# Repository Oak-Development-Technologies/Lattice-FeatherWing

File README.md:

# Lattice FeatherWing
<image src=/images/lattice%20featherwing%20front.jpg>
Home of the Lattice FeatherWing

Lattice FeatherWing is an iCE5LP4K FeatherWing designed to be a companion to any Adafruit compatible feather development board available. Lattice FeatherWing provides 35 IO to 0.1" headers which can be used with dupont 0.1" cables to hook into a companion breadboard.

Interested? You can purchase the Lattice FeatherWing on [Tindie](https://www.tindie.com/products/34549/)

# Quick Facts about Lattice FeatherWing:

* 35 IO Exposed to 0.1" headers 
* 9 IO (including SPI programming pins) directly available to interface with host Feather.
* Small yet bright UHD1110 RGB LED
* 2.5V provided for NVCM programming
* Edge reachable reset button that solely resets the FPGA

# Pinout Card

Provided below is the pinout card that should ship with all Lattice FeatherWing. If you didn't get one, you can always print off the pinout card from the pinout card image in the [images](/images) directory of this repository.

<image src=/images/Lattice%20FeatherWing%20Pincard.jpg>

As noted on the pinout card, each pin on the Lattice FeatherWing corresponds to the phyiscal pin on the FPGA IC. These phyiscal pins are used in the [io.pcf](/examples/common/io.pcf) file to help make it easier for you to pick pins for input/outputs of your verilog designs. These pin numbers can be used to create pin groupings like in the io.pcf file to make it easier to generate your own designs.

# Some Quick Links

You can find some Lattice FeatherWing specific examples by clicking [here](/examples). These examples can be built with the included io.pcf and Makefile by using various make commands. (currently just RGB PWM example available).

In addition to the examples in this repository, you can also find examples for the iCE5LP4K in this [ice5lp4k_examples repository](https://github.com/skerr92/ice5lp4k_examples).

If you're interested in CPU design, you can checkout the [O2 Trainer CPU](https://github.com/skerr92/O2-Trainer).

The KiCAD board files and manufacturing files can be found by clicking [here](/Board%20Files/). These include all the information you need to make your own Lattice FPGA board, or order the files yourself if you want the challenge of making your own.

Lattice FeatherWing is Licensed under [MIT License](LICENSE). This license is permissive, and the contents of this repository come AS IS. Please see the License file for additonal details.

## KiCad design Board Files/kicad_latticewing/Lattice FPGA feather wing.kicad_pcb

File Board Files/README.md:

Find relevant schematic and board files here.

These are the latest revision available, you can open them directly in kicad.

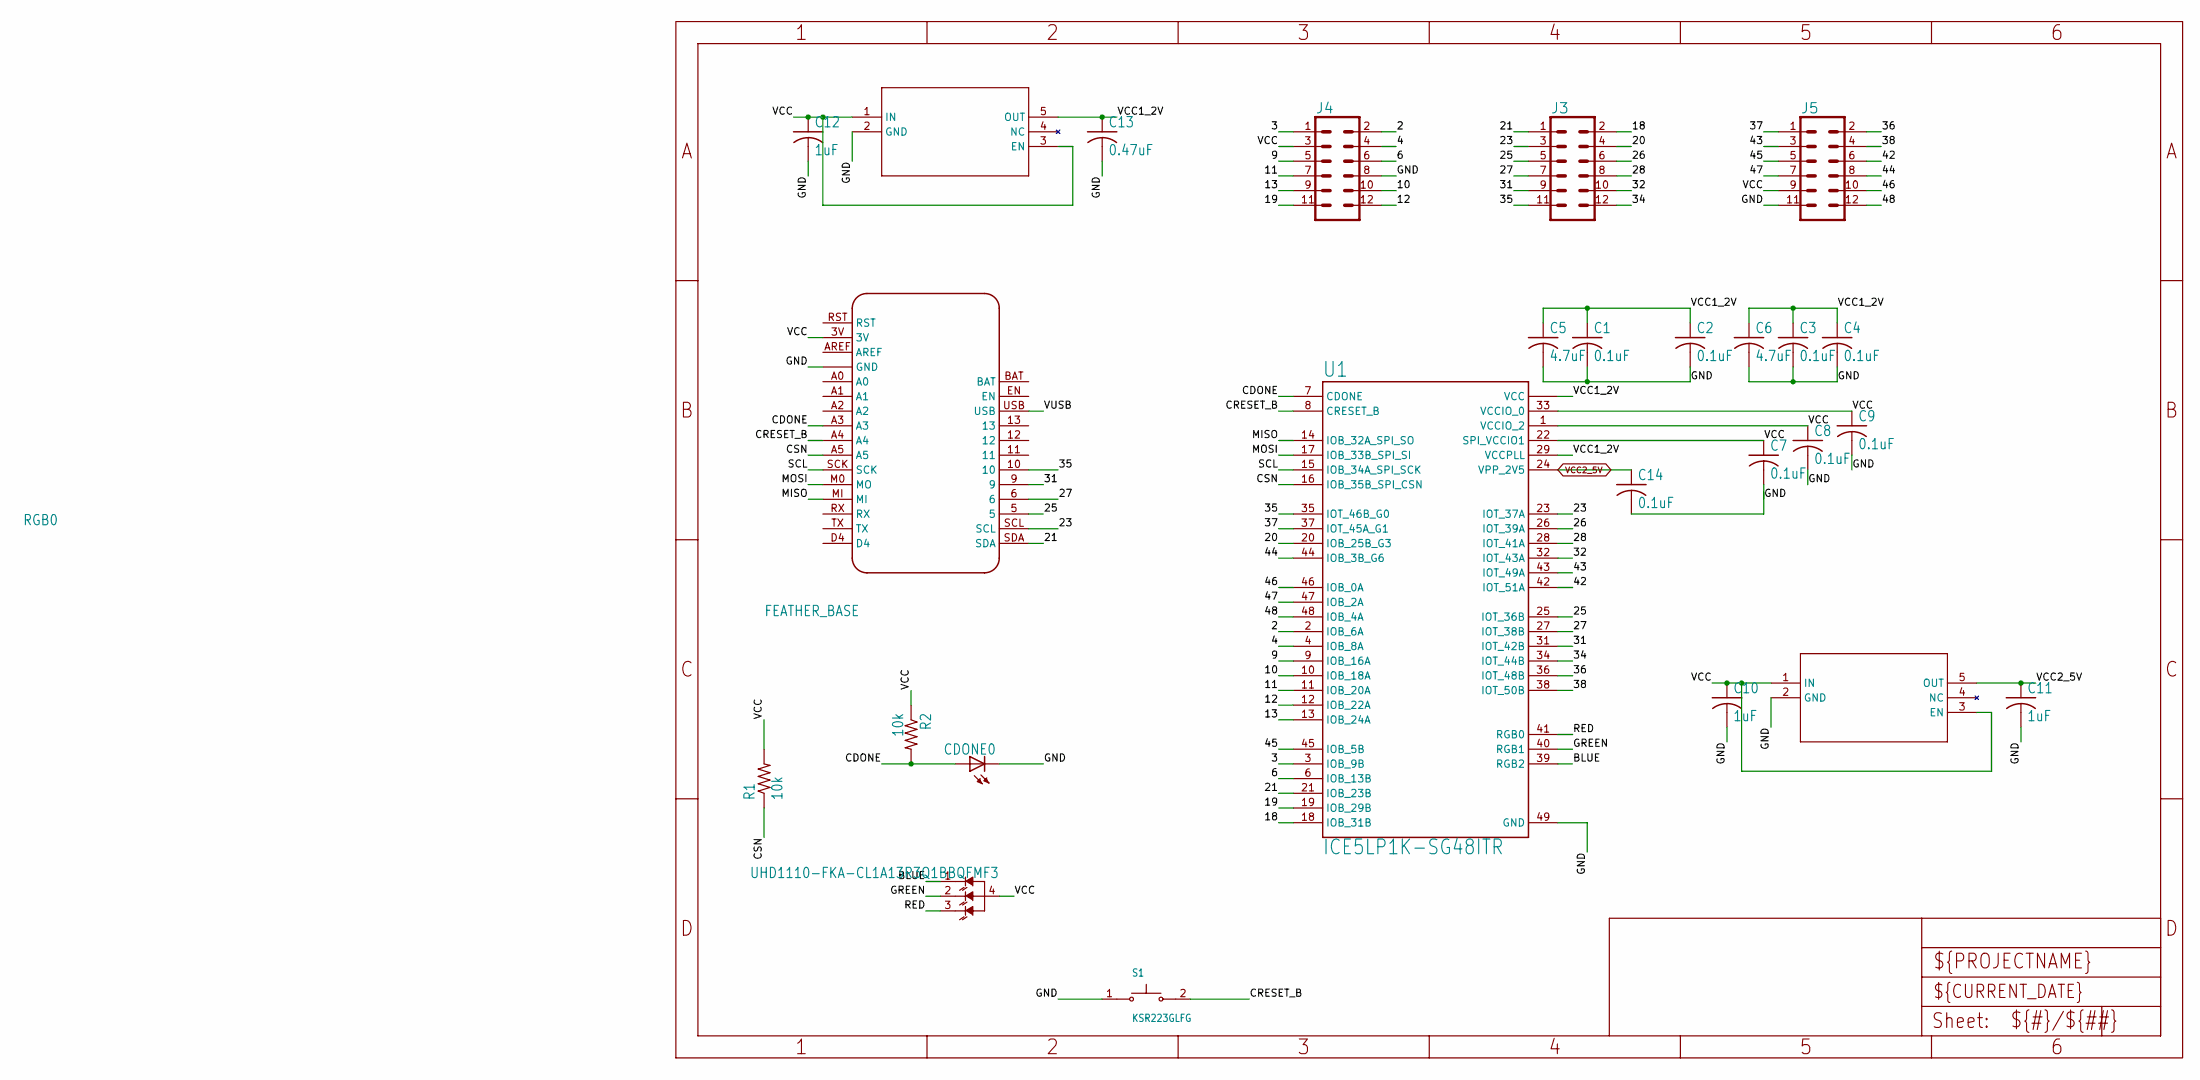
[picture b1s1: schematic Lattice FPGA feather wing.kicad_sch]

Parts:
C1, C2, C3, C4, C7, C8, C9, C14: 0.1uF; C0402
C5, C6: 4.7uF; C0603
C10, C11, C12: 1uF; C0402
C13: 0.47uF; C0402
CDONE0: LEDCHIP-LED0603; CHIP-LED0603
J3, J4, J5: 2X6 FEMALE; 2X6_NOSILK
R1: 10k; R0603
R2: 10k; R0402
RGB0: UHD1110-FKA-CL1A13R3Q1BBQFMF3; LED_UHD1110-FKA-CL1A13R3Q1BBQFMF3
S1: KSR223GLFG; SW_KSR223GLFG
U1: ICE5LP1K-SG48ITR; QFN50P700X700X100-49N
U2, U3: TLV75533PDBVRDBV5_TEX-L; DBV5_TEX-L
U$1: FEATHER_BASE; FEATHER_PINS

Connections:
/2: J4.2, U1.2 (IOB_6A)
/3: J4.1, U1.3 (IOB_9B)
/4: J4.4, U1.4 (IOB_8A)
/6: J4.6, U1.6 (IOB_13B)
/9: J4.5, U1.9 (IOB_16A)
/10: J4.10, U1.10 (IOB_18A)
/11: J4.7, U1.11 (IOB_20A)
/12: J4.12, U1.12 (IOB_22A)
/13: J4.9, U1.13 (IOB_24A)
/18: J3.2, U1.18 (IOB_31B)
/19: J4.11, U1.19 (IOB_29B)
/20: J3.4, U1.20 (IOB_25B_G3)
/21: J3.1, U1.21 (IOB_23B), U$1.SDA
/23: J3.3, U1.23 (IOT_37A), U$1.SCL
/25: J3.5, U1.25 (IOT_36B), U$1.5
/26: J3.6, U1.26 (IOT_39A)
/27: J3.7, U1.27 (IOT_38B), U$1.6
/28: J3.8, U1.28 (IOT_41A)
/31: J3.9, U1.31 (IOT_42B), U$1.9
/32: J3.10, U1.32 (IOT_43A)
/34: J3.12, U1.34 (IOT_44B)
/35: J3.11, U1.35 (IOT_46B_G0), U$1.10
/36: J5.2, U1.36 (IOT_48B)
/37: J5.1, U1.37 (IOT_45A_G1)
/38: J5.4, U1.38 (IOT_50B)
/42: J5.6, U1.42 (IOT_51A)
/43: J5.3, U1.43 (IOT_49A)
/44: J5.8, U1.44 (IOB_3B_G6)
/45: J5.5, U1.45 (IOB_5B)
/46: J5.10, U1.46 (IOB_0A)
/47: J5.7, U1.47 (IOB_2A)
/48: J5.12, U1.48 (IOB_4A)
/BLUE: RGB0.1 (BLUE), U1.39 (RGB2)
/CDONE: CDONE0.A, R2.2, U1.7 (CDONE), U$1.A3
/CRESET_B: S1.2, U1.8 (CRESET_B), U$1.A4
/CSN: R1.1, U1.16 (IOB_35B_SPI_CSN), U$1.A5
/GND: C1.2, C2.2, C3.2, C4.2, C5.2, C6.2, C7.2, C8.2, C9.2, C10.2, C11.2, C12.2, C13.2, C14.2, CDONE0.C, J4.8, J5.11, S1.1, U1.49 (GND), U2.2 (GND), U3.2 (GND), U$1.GND, U$1.P$1 (GND), U$1.P$2 (GND)
/GREEN: RGB0.2 (GREEN), U1.40 (RGB1)
/MISO: U1.14 (IOB_32A_SPI_SO), U$1.MI
/MOSI: U1.17 (IOB_33B_SPI_SI), U$1.M0 (MO)
/RED: RGB0.3 (RED), U1.41 (RGB0)
/SCL: U1.15 (IOB_34A_SPI_SCK), U$1.SCK
/VCC: C7.1, C8.1, C9.1, C10.1, C12.1, J4.3, J5.9, R1.2, R2.1, RGB0.4 (ANODE), U1.1 (VCCIO_2), U1.22 (SPI_VCCIO1), U1.33 (VCCIO_0), U2.1 (IN), U2.3 (EN), U3.1 (IN), U3.3 (EN), U$1.3V
/VCC1_2V: C1.1, C2.1, C3.1, C4.1, C5.1, C6.1, C13.1, U1.5 (VCC), U1.29 (VCCPLL), U1.30 (VCC), U2.5 (OUT)
/VUSB: U$1.USB
VCC2_5V: C11.1, C14.1, U1.24 (VPP_2V5), U3.5 (OUT)

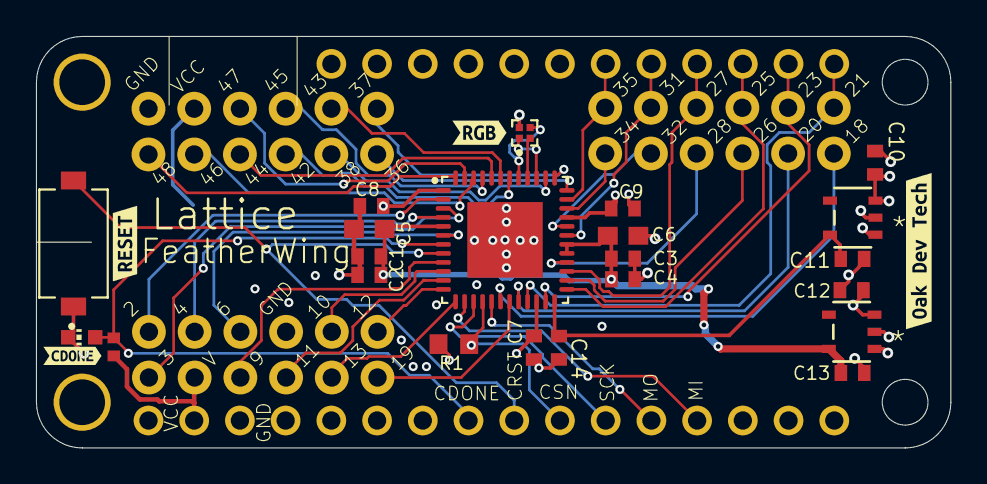
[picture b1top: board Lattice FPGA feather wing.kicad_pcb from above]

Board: 4 copper layers, 50.8 x 22.9 mm, 30 parts (0 on the bottom side), 45 nets.

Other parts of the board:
kibuzzard-661C746D: G***; kibuzzard-661C746D
kibuzzard-661C7431: G***; kibuzzard-661C7431
kibuzzard-661C7456: G***; kibuzzard-661C7456
kibuzzard-662D2453: G***; kibuzzard-662D2453

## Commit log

2024-05-08 Create Makefile
2024-05-20 add at least one example.:
2024-05-20 add image to top
2024-05-26 Add more to the repository
2024-05-26 add links to additional examples and repos
2024-05-26 add tindie shop link
